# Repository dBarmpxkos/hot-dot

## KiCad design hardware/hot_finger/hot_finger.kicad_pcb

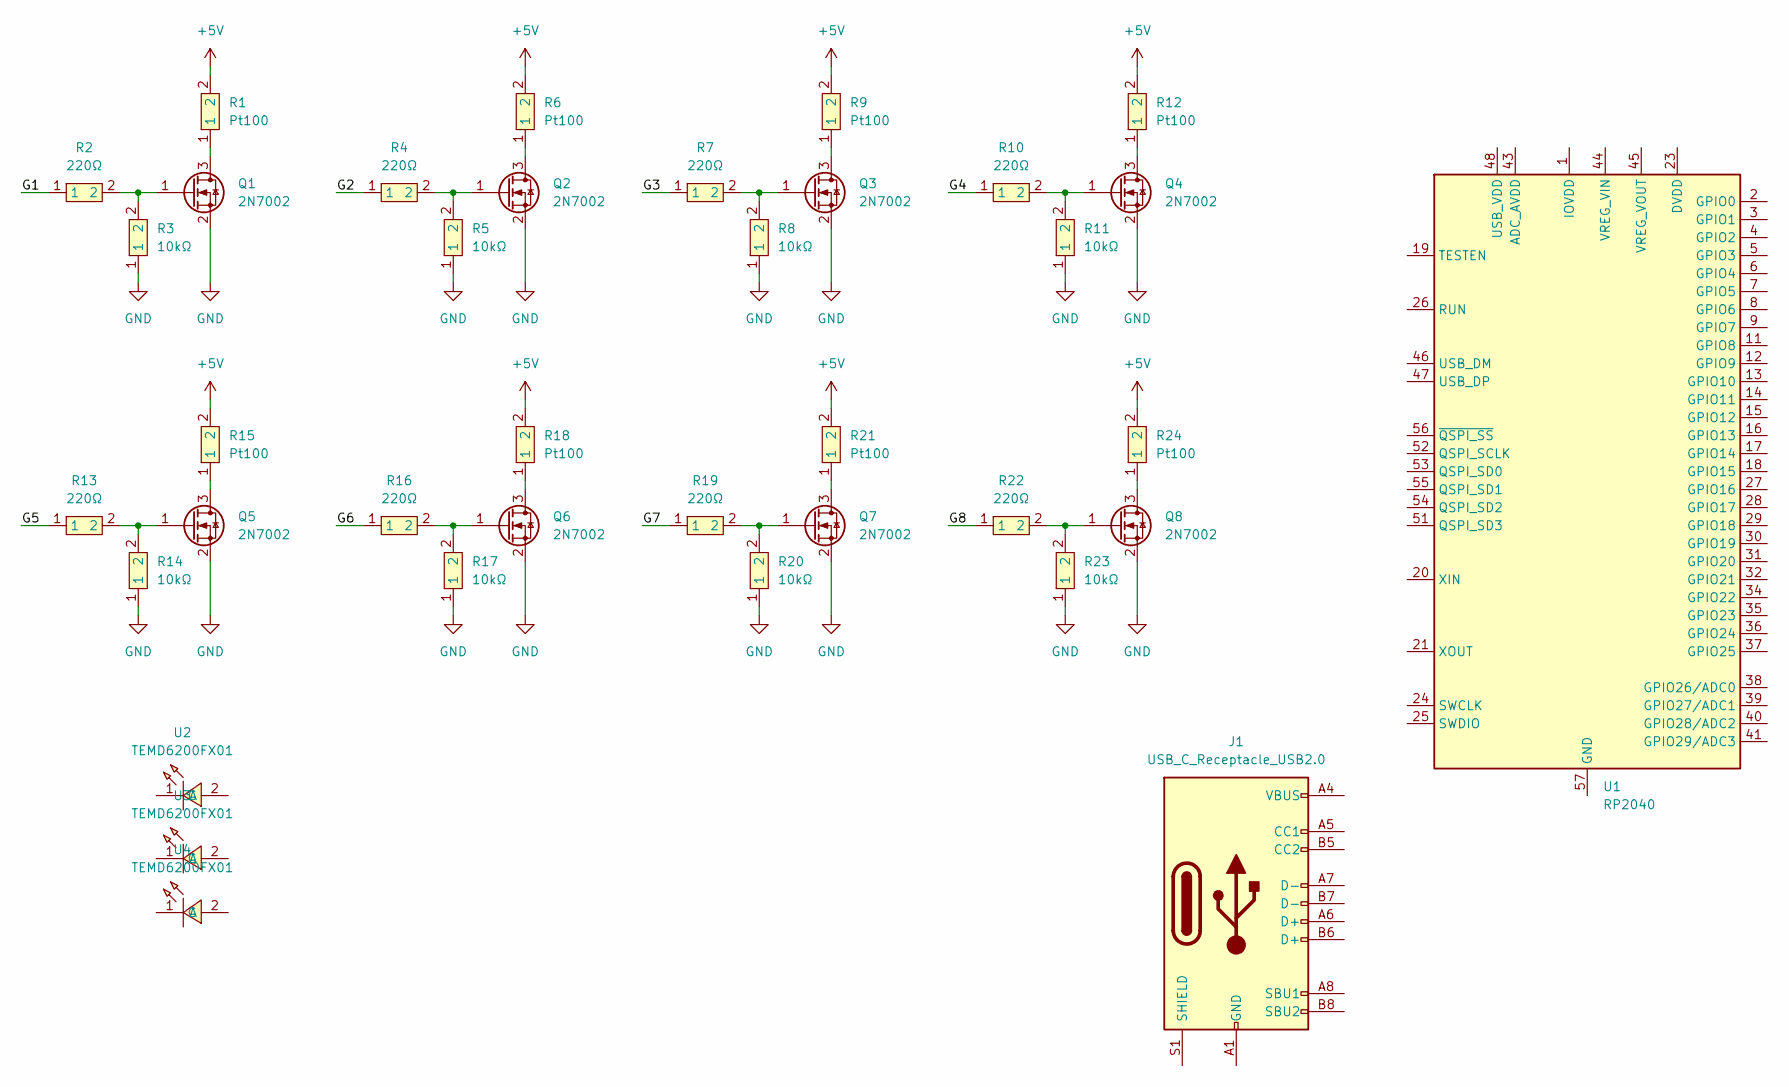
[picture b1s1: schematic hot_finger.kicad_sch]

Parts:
J1: USB_C_Receptacle_USB2.0; USB_C_Receptacle_HRO_TYPE-C-31-M-12
Q1, Q2, Q3, Q4, Q5, Q6, Q7, Q8: 2N7002; SOT-23
R1, R2, R3, R4, R5, R6, R7, R8, R9, R10, R11, R12, R13, R14, R15, R16, R17, R18, R19, R20, R21, R22, R23, R24: 0402 ±1% 10K; R0402; LCSC Part C2889342
U1: RP2040; QFN-56-1EP_7x7mm_P0.4mm_EP3.2x3.2mm
U2, U3, U4: TEMD6200FX01; OPTO-SMD_L2.0-W1.3-RD-1; MPN TEMD6200FX01; LCSC Part C499517

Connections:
+5V: R1.2, R6.2, R9.2, R12.2, R15.2, R18.2, R21.2, R24.2
/G1: R2.1
/G2: R4.1
/G3: R7.1
/G4: R10.1
/G5: R13.1
/G6: R16.1
/G7: R19.1
/G8: R22.1
GND: Q1.2 (S), Q2.2 (S), Q3.2 (S), Q4.2 (S), Q5.2 (S), Q6.2 (S), Q7.2 (S), Q8.2 (S), R3.1, R5.1, R8.1, R11.1, R14.1, R17.1, R20.1, R23.1
unnamed: J1.A1 (GND), J1.A12 (GND), J1.B1 (GND), J1.B12 (GND)
unnamed: J1.A4 (VBUS), J1.A9 (VBUS), J1.B4 (VBUS), J1.B9 (VBUS)
unnamed: Q1.3 (D), R1.1
unnamed: Q1.1 (G), R2.2, R3.2
unnamed: Q2.3 (D), R6.1
unnamed: Q2.1 (G), R4.2, R5.2
unnamed: Q3.3 (D), R9.1
unnamed: Q3.1 (G), R7.2, R8.2
unnamed: Q4.3 (D), R12.1
unnamed: Q4.1 (G), R10.2, R11.2
unnamed: Q5.3 (D), R15.1
unnamed: Q5.1 (G), R13.2, R14.2
unnamed: Q6.3 (D), R18.1
unnamed: Q6.1 (G), R16.2, R17.2
unnamed: Q7.3 (D), R21.1
unnamed: Q7.1 (G), R19.2, R20.2
unnamed: Q8.3 (D), R24.1
unnamed: Q8.1 (G), R22.2, R23.2
unnamed: U1.23 (DVDD), U1.50 (DVDD)
unnamed: U1.1 (IOVDD), U1.10 (IOVDD), U1.22 (IOVDD), U1.33 (IOVDD), U1.42 (IOVDD), U1.49 (IOVDD)

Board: 2 copper layers, 37 parts (12 on the bottom side), 22 nets, no tracks yet.

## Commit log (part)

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2026-04-20 doc: add initial files, add gitignore, add lfs
2026-04-20 feature: add photodiodes
2026-04-20 feature: add website prototype
2026-04-20 feature: update website info
2026-04-20 Add preliminary website link to README
2026-05-04 feature: add site
